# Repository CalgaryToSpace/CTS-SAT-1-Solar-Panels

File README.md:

# CTS-SAT-1-Solar-Panels

Solar panel PCB designs for the CTS-SAT-1 (FrontierSat) 3U cubesat

## Solar Panel Overview
* 4x COTS 2U solar panels are the main power generation for the satellite. Model: [NPC SpaceMind](https://www.npcspacemind.com) SM-SP2X.
* As a proof of concept, the following panels are manufactured in-house (designed contained in this repo):
    * 2x 1.25U panels
    * 1x 1.0U panel

The `rev3` release/tag, with PCBs manufactured by AISLER, is flown on CTS-SAT-1.

## 1.25U Solar Panel

* 30 cells, in a 6S5P configuration (6 cells in each string, then joined in parallel).

## Bill of Materials (Highlights)
* PMEG3010EP diodes in a SOD128 package (low VF Schottky barrier rectifier)
* [AA-DUCT 902 Silver Epoxy Adhesive](https://atomadhesives.com/aa-duct-902-silver-epoxy-adhesive-electrically-conductive-room-temp-curing-air-dr/)
* KXOB25-05X3F solar cells
    * Nominal efficiency: 25%
    * Monocrystalline, silicon composition
    * Very cost-efficient

## Solar Panel Assembly Steps
Work in the Laminar Flow Table with proper ESD protection. Wear gloves. Be careful with fragile cells.

1. Assemble SMD solder components.
2. Clean solar panel PCB with isopropyl alcohol (clean flux residue).
3. Put epoxy in hot water for 10 minutes (get epoxy to around 40C, warm-to-touch).
4. Massage epoxy in pouch, following epoxy supplier's guidelines.
5. Get out the solar cells.
6. Apply some epoxy to solar panel pads.
7. Take a picture of the application for reference on future applications.
8. Use the suction tool or hands to place solar cells on the panels. Press down on each cell.
9. Wait 24h for epoxy to dry.

## License
This project is licensed under the [CERN OHL v2 Permissive](https://choosealicense.com/licenses/cern-ohl-p-2.0/) license. We appreciate attribution and links back, but you are free to do what you wish with this project.

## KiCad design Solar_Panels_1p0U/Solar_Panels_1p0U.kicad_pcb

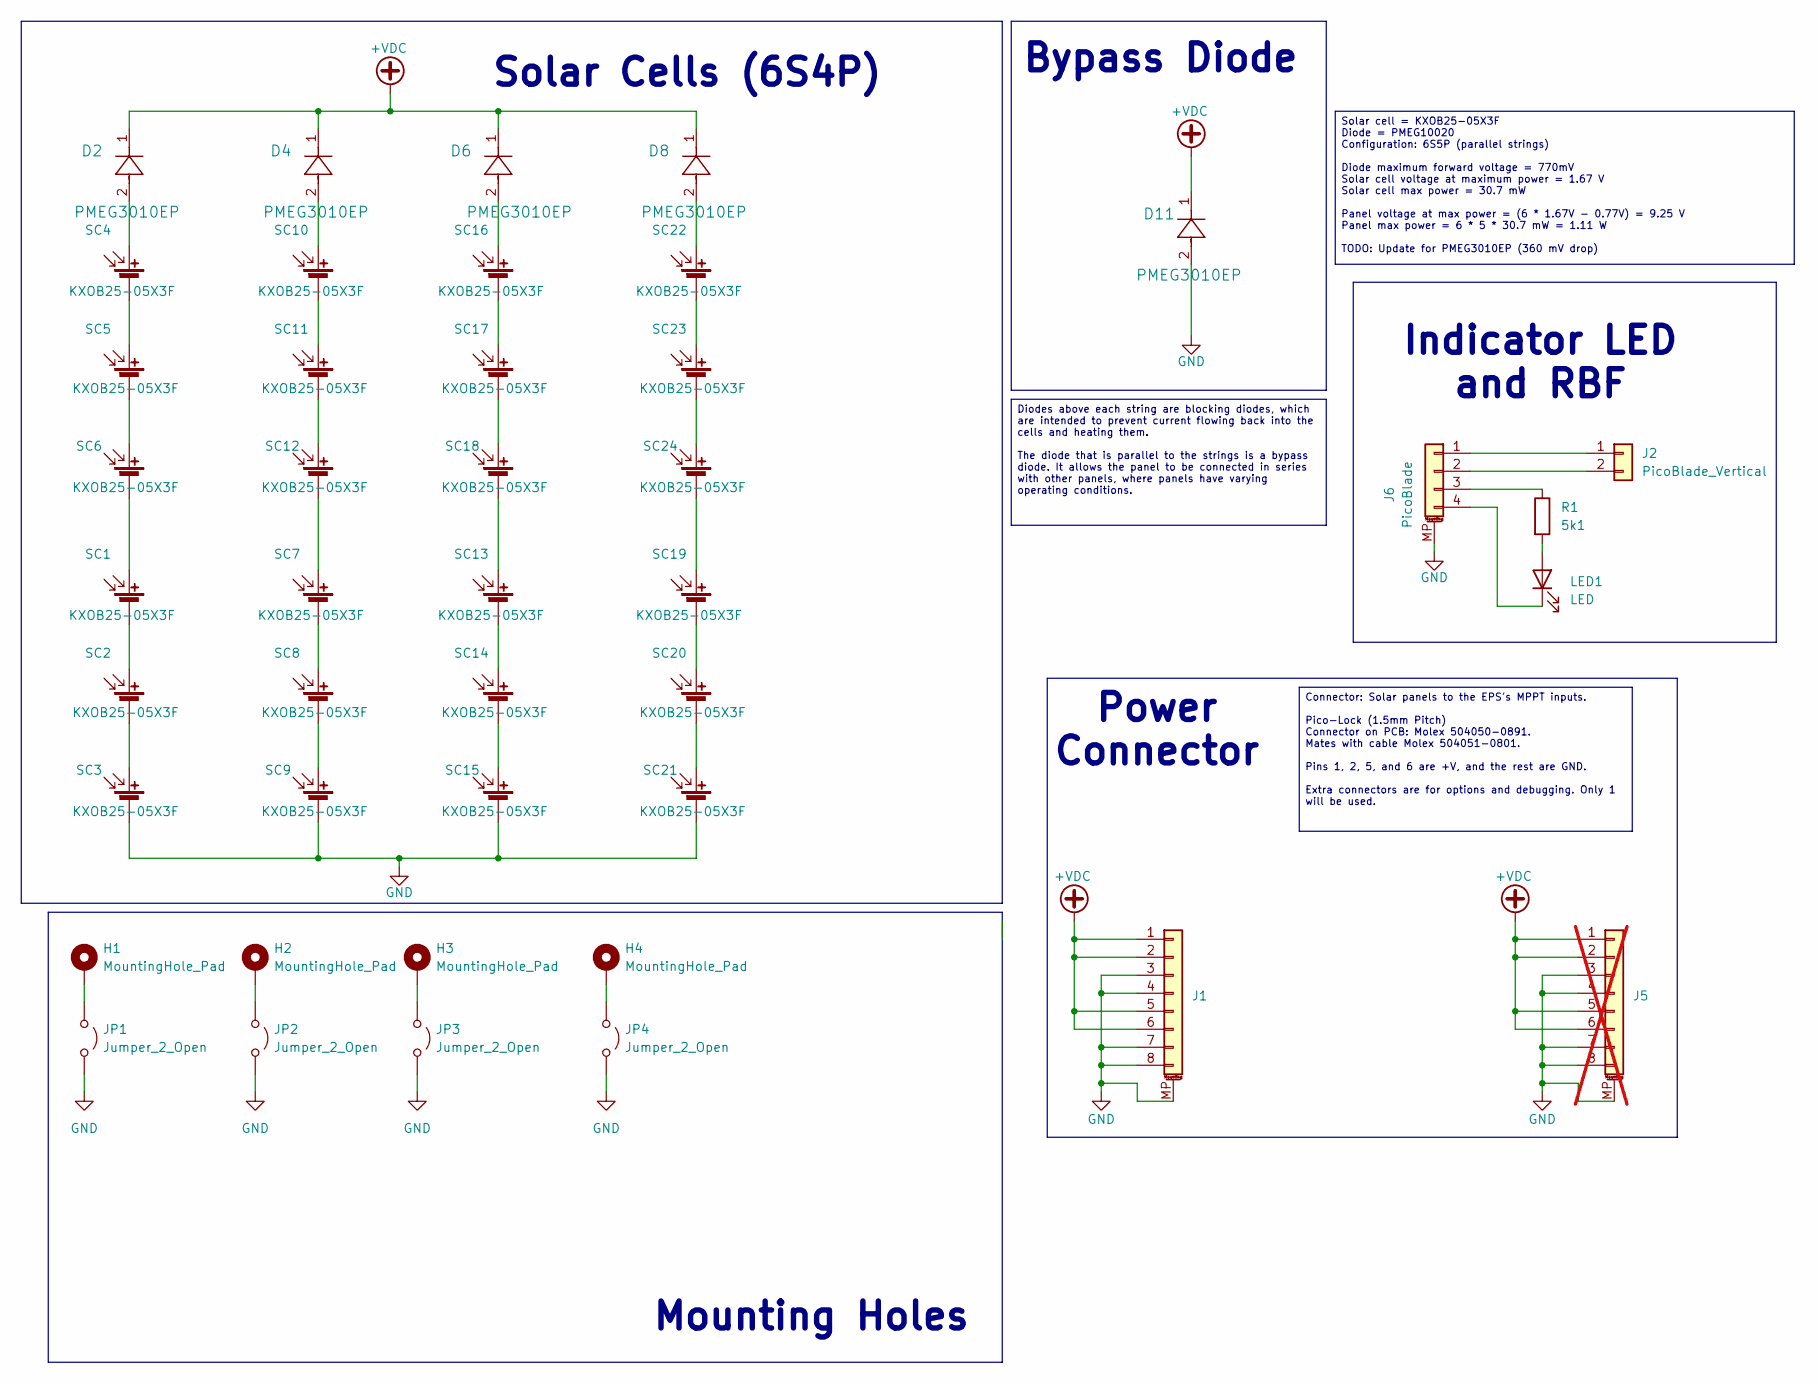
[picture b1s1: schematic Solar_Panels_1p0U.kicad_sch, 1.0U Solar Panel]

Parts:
D2, D4, D6, D8, D11: PMEG3010EP; PMEG10020AELPX
H1, H2, H3, H4: MountingHole_Pad; MountingHole_3.2mm_M3_DIN965_Pad
J1: Conn_01x08_MountingPin; Molex_PicoBlade_53261-0871_1x08-1MP_P1.25mm_Horizontal
J2: PicoBlade_Vertical; Molex_PicoBlade_53047-0210_1x02_P1.25mm_Vertical
J5: Conn_01x08_MountingPin; Molex_Pico-Lock_504050-0891_1x08-1MP_P1.50mm_Horizontal; not fitted
J6: PicoBlade; Molex_PicoBlade_53261-0471_1x04-1MP_P1.25mm_Horizontal
JP1, JP2, JP3, JP4: Jumper_2_Open; SolderJumper-2_P1.3mm_Open_Pad1.0x1.5mm
LED1: LED; LED_0603_1608Metric_Pad1.05x0.95mm_HandSolder
R1: 5k1; R_0603_1608Metric_Pad0.98x0.95mm_HandSolder
SC1, SC2, SC3, SC4, SC5, SC6, SC7, SC8, SC9, SC10, SC11, SC12, SC13, SC14, SC15, SC16, SC17, SC18, SC19, SC20, SC21, SC22, SC23, SC24: KXOB25-05X3F

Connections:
+VDC: D2.1, D4.1, D6.1, D8.1, D11.1, J1.1, J1.2, J1.5, J1.6, J5.1, J5.2, J5.5, J5.6
GND: D11.2, J1.3, J1.4, J1.7, J1.8, J1.MP (MountPin), J5.3, J5.4, J5.7, J5.8, J5.MP (MountPin), J6.MP (MountPin), JP1.2 (B), JP2.2 (B), JP3.2 (B), JP4.2 (B), SC3.2 (-), SC9.2 (-), SC15.2 (-), SC21.2 (-)
unnamed: J2.1, J6.1
unnamed: J2.2, J6.2
unnamed: J6.3, R1.1
unnamed: J6.4, LED1.1 (K)
unnamed: H1.1, JP1.1 (A)
unnamed: H2.1, JP2.1 (A)
unnamed: H3.1, JP3.1 (A)
unnamed: H4.1, JP4.1 (A)
unnamed: LED1.2 (A), R1.2
unnamed: SC1.1 (+), SC6.2 (-)
unnamed: SC1.2 (-), SC2.1 (+)
unnamed: SC2.2 (-), SC3.1 (+)
unnamed: D2.2, SC4.1 (+)
unnamed: SC4.2 (-), SC5.1 (+)
unnamed: SC5.2 (-), SC6.1 (+)
unnamed: SC7.2 (-), SC8.1 (+)
unnamed: SC8.2 (-), SC9.1 (+)
unnamed: D4.2, SC10.1 (+)
unnamed: SC10.2 (-), SC11.1 (+)
unnamed: SC11.2 (-), SC12.1 (+)
unnamed: SC7.1 (+), SC12.2 (-)
unnamed: SC13.1 (+), SC18.2 (-)
unnamed: SC13.2 (-), SC14.1 (+)
unnamed: SC14.2 (-), SC15.1 (+)
unnamed: D6.2, SC16.1 (+)
unnamed: SC16.2 (-), SC17.1 (+)
unnamed: SC17.2 (-), SC18.1 (+)
unnamed: SC19.1 (+), SC24.2 (-)
unnamed: SC19.2 (-), SC20.1 (+)
unnamed: SC20.2 (-), SC21.1 (+)
unnamed: D8.2, SC22.1 (+)
unnamed: SC22.2 (-), SC23.1 (+)
unnamed: SC23.2 (-), SC24.1 (+)

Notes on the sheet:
Power Connector
Mounting Holes
Bypass Diode
Indicator LED and RBF
Solar Cells (6S4P)
Diodes above each string are blocking diodes, which are intended to prevent current flowing back into the cells and heating them. The diode that is parallel to the strings is a bypass diode. It allows the panel to be connected in series with other panels, where panels have varying operating conditi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
Connector: Solar panels to the EPS's MPPT inputs. Pico-Lock (1.5mm Pitch) Connector on PCB: Molex 504050-0891. Mates with cable Molex 504051-0801. Pins 1, 2, 5, and 6 are +V, and the rest are GND. Extra connectors are for options and debugging. Only 1 will be used.
Solar cell = KXOB25-05X3F Diode = PMEG10020 Configuration: 6S5P (parallel strings) Diode maximum forward voltage = 770mV Solar cell voltage at maximum power = 1.67 V Solar cell max power = 30.7 mW Panel voltage at max power = (6 * 1.67V - 0.77V) = 9.25 V Panel max power = 6 * 5 * 30.7 mW = 1.11 W T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

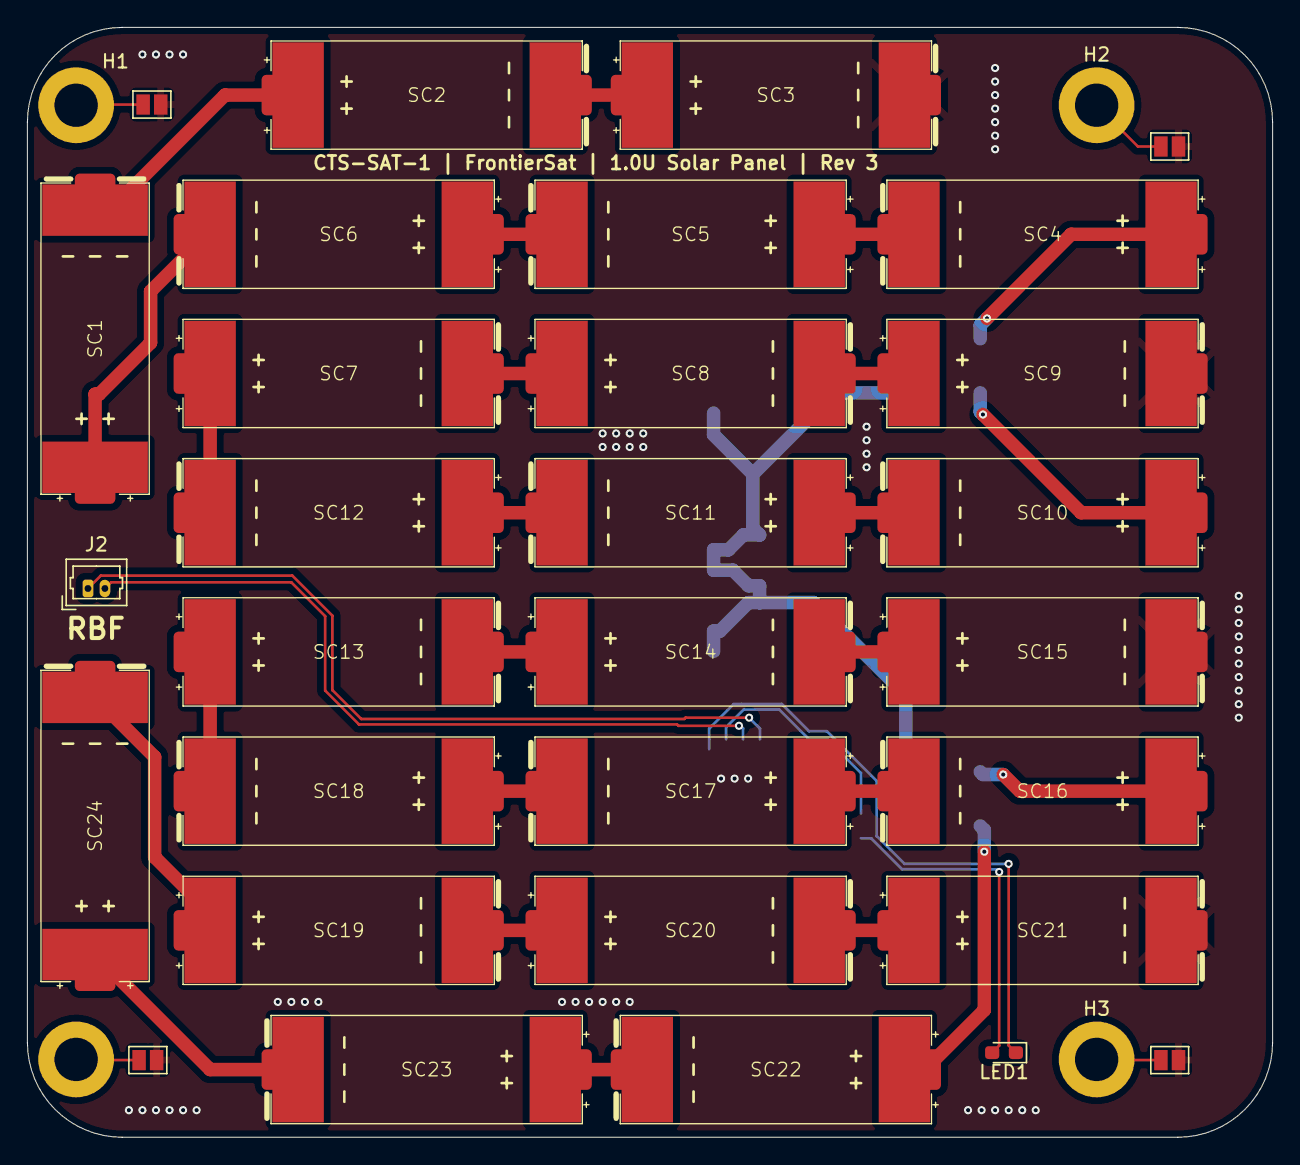
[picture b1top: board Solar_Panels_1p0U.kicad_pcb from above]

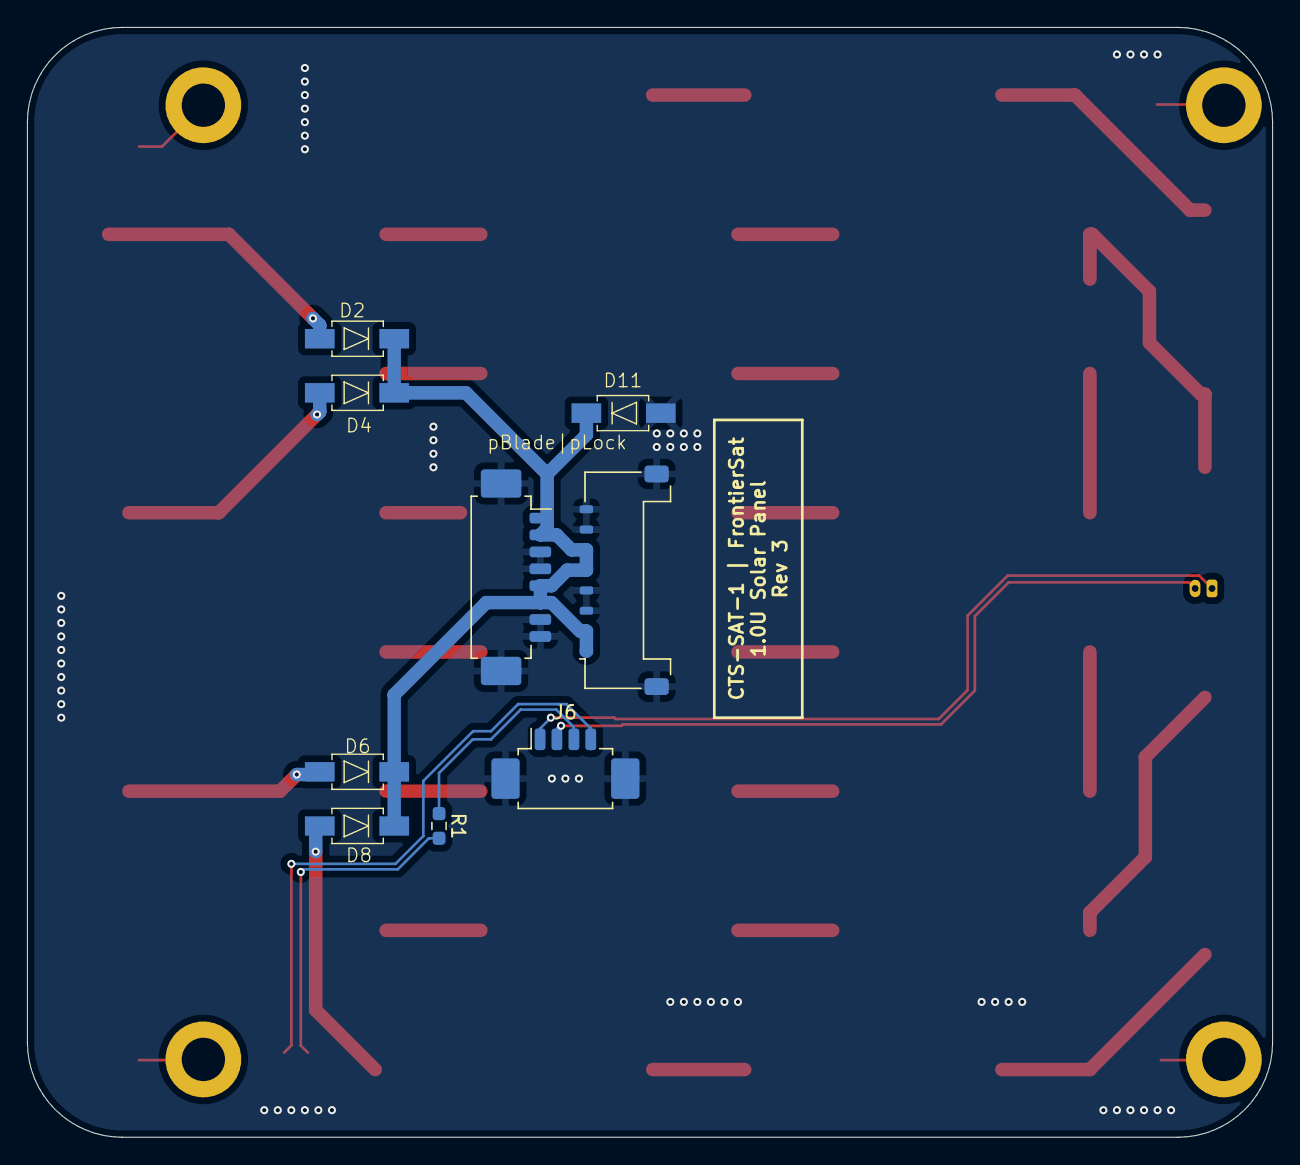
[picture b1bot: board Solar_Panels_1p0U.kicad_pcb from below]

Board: 2 copper layers, 92.0 x 82.0 mm, 43 parts (9 on the bottom side), 35 nets.

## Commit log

2024-01-15 Add license and overview info
2024-01-15 Create gitignore for Altium
    Source: https://raw.githubusercontent.com/Fermium/altium-on-git/master/.gitignore
2024-01-16 Added latest Solar Panel PCB rev from Frank.
2024-01-16 Added the latest schematic for the Solar Panel using Gochermann Cells
2024-01-16 Updated PCB rev to latest
2024-01-16 Add a couple notes to README
2024-01-16 Updating the README file, Updating the Rev5.9 Solar Panel PCB doc.
2024-01-16 Added Schematic symbol libraries, added PCB footprint libraries, and latest schematic doc.
2024-01-16 Rearranged and added folders for organization
2024-01-16 Updated file name
2024-01-16 Updated PCB doc
2024-01-17 Updated mounting hole placements, reviewed with Structural team.
2024-01-18 Added latest 3U solar panel design Frank was working on. This 3U solar panel design is NOT done.
2024-01-18 Added latest 3U schematics. NOTE: These designs are incomplete, as they have previous solar cells, previous EPS connector, and not shadow protection diode.
2024-01-27 Solar Panel Rev 5.9 2U PCB ORDER PLACED - Pcbdoc, Gerber files, and invoice placed in the 2U_designs folder. Created 2U and 3U design folders in branch.
2024-01-28 Updated the Gerber and Drill files for the Order placed yesterday, January 27th. Revision of 2U PCB used is still Rev 5.9.
2024-07-13 Add KiCAD Gitignore
2024-07-13 Initial Design
    Design before being revised by Parker and Dr. Nacho
2024-07-17 Updated Initial Panels
    Updated a bit of the routing before Parker and Nacho takes a look at it. Put the connector on the inside.
2024-07-17 Initial Panels Revision
    Changed the Solar Panels to adjust to structural needs.
2024-07-17 Updated Solar Panels
    Revised to fit Brett's preferences.
2024-07-24 Modifications For 2U Panels
    Made structural modifications to suit Brett's structure and tried to improve the PCB board based on Parker's suggestions. Schematic is extremely wonky right now but will try to fix it ASAP.
2024-07-30 Diodes changes and adjusted schematic.
    Made the diode changes based off Parker's suggestions and fixed the schematic. Comments are now included within the schematic.
2024-07-31 Quick Adjustments to Schematic and Routing
    Adjusted so there's only one bypass diode for the entire panel. Made changes to the routing as well.
2024-08-01 Add diode name to README quickly
2024-08-06 Routed the PCB after the Footprint Adjustments
    Routed the PCB after making adjustments to the TriSolX footprint.
2024-08-07 PDF Schematic
    Created a PDF Schematic for review.
2024-08-07 Added Vdc Info
    Quick schematic change to indicate vdc.
2024-08-07 more information added to schematic
    added more info for the voltages
2024-08-10 Refined Simons 2u
    I tried refining Simons design a bit and aligned the holes/dimensions to the most current frame version.
    Looking good on the structural side. Think we just need a last electrical review then should be ready to order.
2024-08-10 Started 1U Solar Panels Design
    Begun to start on the 1U design.
2024-08-14 Schematic Finished for 1U Panel
    Title
2024-08-17 Small schematic cleanup
2024-08-17 Improve footprints, layout, routing
2024-08-17 Add render to README
2024-08-20 August 20th Changes
    Finished setting up the PCB board (haven't started the PCB board yet)
2024-08-21 Finished initial draft of the 1U
    Finished routing initial 1U draft to be reviewed by Parker and structural.
2024-08-24 Changed the footprint of the solar panels a tiny bit
    Changed the footprints so that the keepout zone is a tiny bit bigger.
2024-08-24 Adjusted some placements and the footprint
    Made some adjustments to the footprint (changing placement of the throughhole and the placement of solar cells)
2024-08-25 Made adjustments to Trisolx footprint and rerouted
2024-08-27 Adjust layout, add back-side cross-board pour
2024-08-27 Add dimensioning drawings and comments
2024-08-28 Reorganize lib and rename project to Solar_Panels_1p25U
2024-08-28 Add diode name to README (#6)
2024-08-28 Reorganize 1U panels
2024-08-28 Create initial 1U revision (#7)
    * Started 1U Solar Panels Design
    Begun to start on the 1U design.
    * Schematic Finished for 1U Panel
    Title
    * August 20th Changes
    Finished setting up the PCB board (haven't started the PCB board yet)
2024-08-28 Prep Rev 1 release
2025-03-12 Kicad 9.0 PCB UPDATE
2025-03-12 1u Updates
2025-03-19 Fixed diode placement and rerouted
2025-03-29 Add files via upload
    Added logo, revision number, date, and label to PCB. Updated the revision date and revision number on the schematic and PCB
2025-04-19 Design new Rev 2 solar panel with new cells
2025-04-22 Finish routing
2025-04-22 Update footprints with extra protuding pads for testing
2025-04-22 Finalize Rev 2
2025-04-22 docs: Update render of 1.25U panel
2025-05-09 Update diode model and description
2025-05-09 1.25U: Fix typo on connector label
2025-05-09 1.0U: Layout cells
2025-05-09 1.0U: Finalize layout mostly
2025-05-10 1.0U: More layout and routing
2025-05-10 Finish Rev 3 - 1.0U
2025-05-10 Finalize Rev 3 of both panels
2025-09-24 docs: clarify assembly and BOM in final CTS-SAT-1 assembly
